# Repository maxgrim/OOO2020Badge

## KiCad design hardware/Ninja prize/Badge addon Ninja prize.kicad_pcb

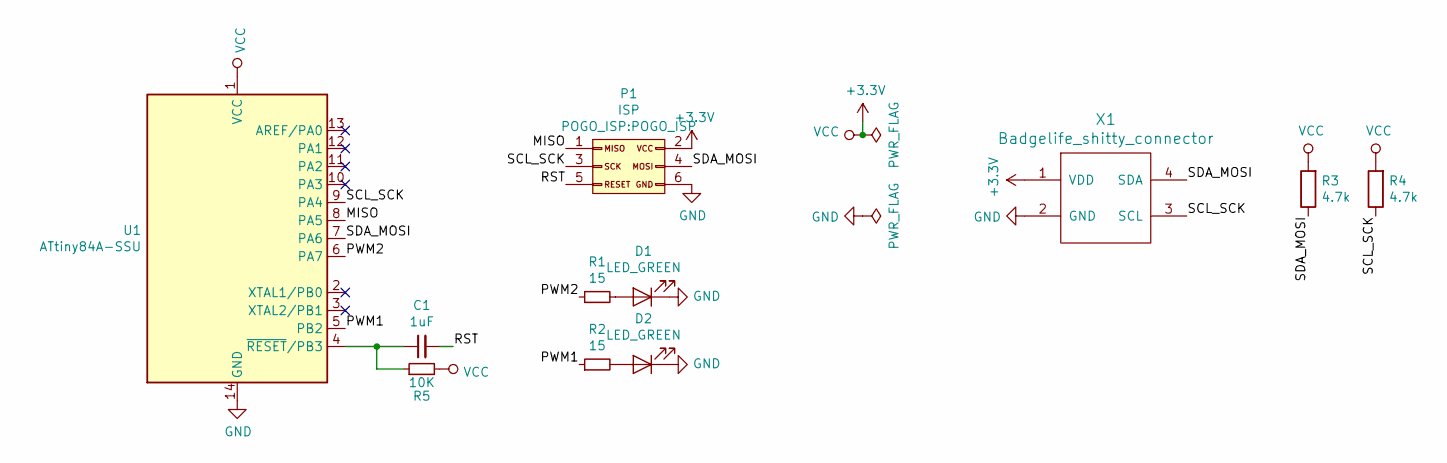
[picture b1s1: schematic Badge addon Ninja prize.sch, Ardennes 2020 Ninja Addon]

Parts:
C1: 1uF; C_0603_1608Metric; LCSC Part C15849
D1, D2: LED_GREEN; LED_1206_3216Metric_Castellated; LCSC Part C375461
P1: ISP; POGO_ISP; JLCPCB BOM 0
R1, R2: 15; R_0603_1608Metric; LCSC Part C23204
R3, R4: 4.7k; R_0603_1608Metric; LCSC Part C23162
R5: 10K; R_0603_1608Metric; LCSC Part C15401
U1: ATtiny84A-SSU; SOIC-14_3.9x8.7mm_P1.27mm; LCSC Part C144333
X1: Badgelife_shitty_connector; Badgelife-Shitty-2x2; JLCPCB BOM 0

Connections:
+3V3: P1.2, R3.2, R4.2, R5.2, U1.1 (VCC), X1.1 (VDD)
/MISO: P1.1, U1.8 (PA5)
/PWM1: R2.1, U1.5 (PB2)
/PWM2: R1.1, U1.6 (PA7)
/RST: C1.2, P1.5
/SCL_SCK: P1.3, R4.1, U1.9 (PA4), X1.3 (SCL)
/SDA_MOSI: P1.4, R3.1, U1.7 (PA6), X1.4 (SDA)
GND: D1.1 (K), D2.1 (K), P1.6, U1.14 (GND), X1.2 (GND)
unnamed: C1.1, R5.1, U1.4 (~RESET~/PB3)
unnamed: D1.2 (A), R1.2
unnamed: D2.2 (A), R2.2

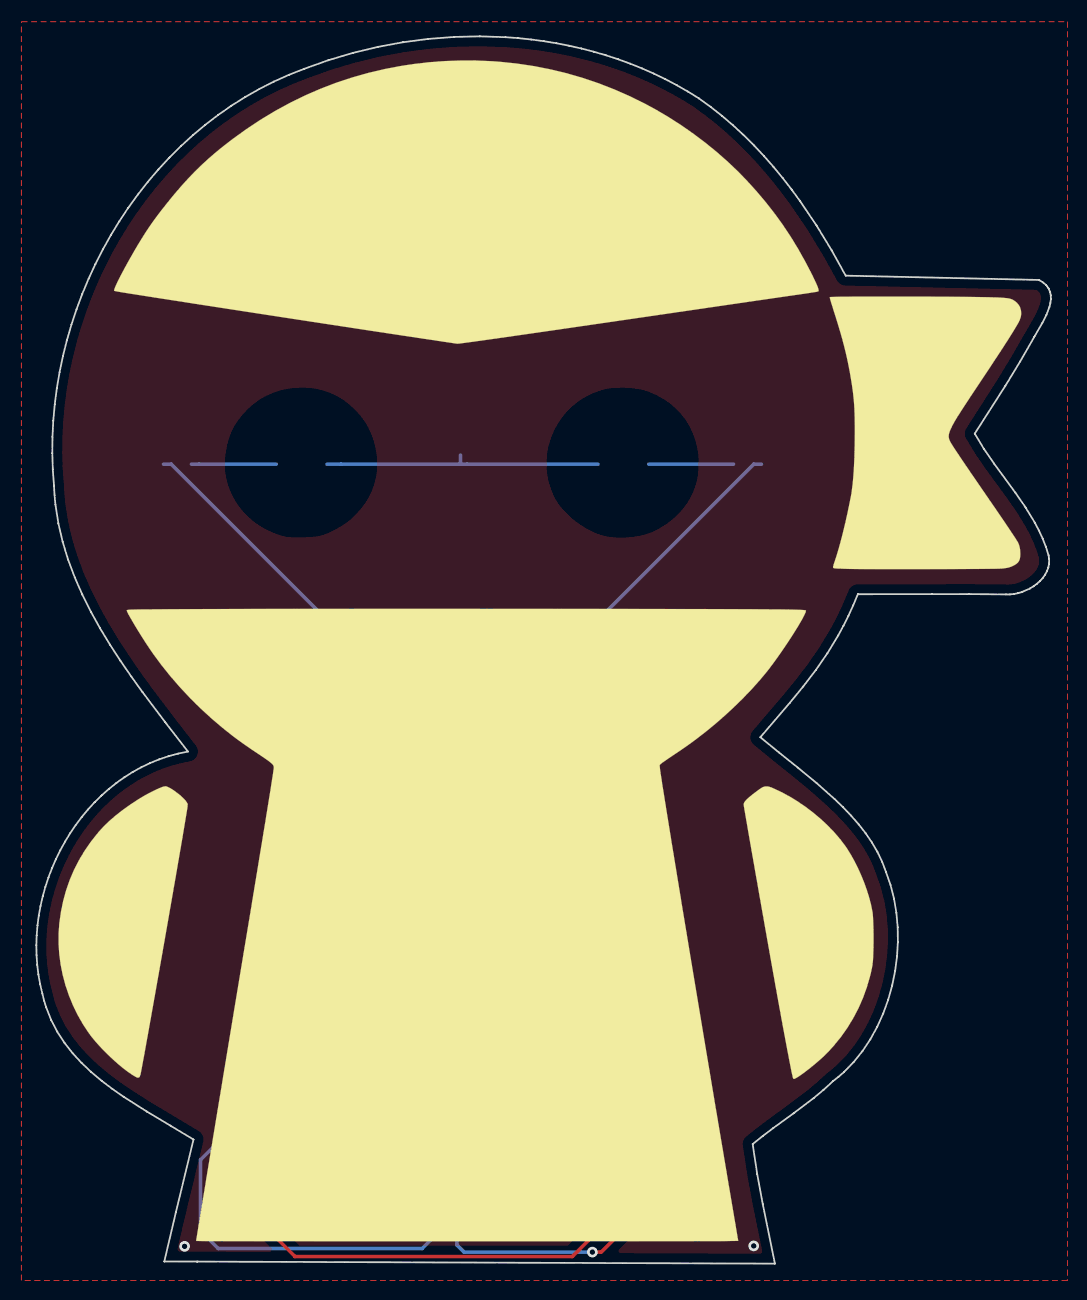
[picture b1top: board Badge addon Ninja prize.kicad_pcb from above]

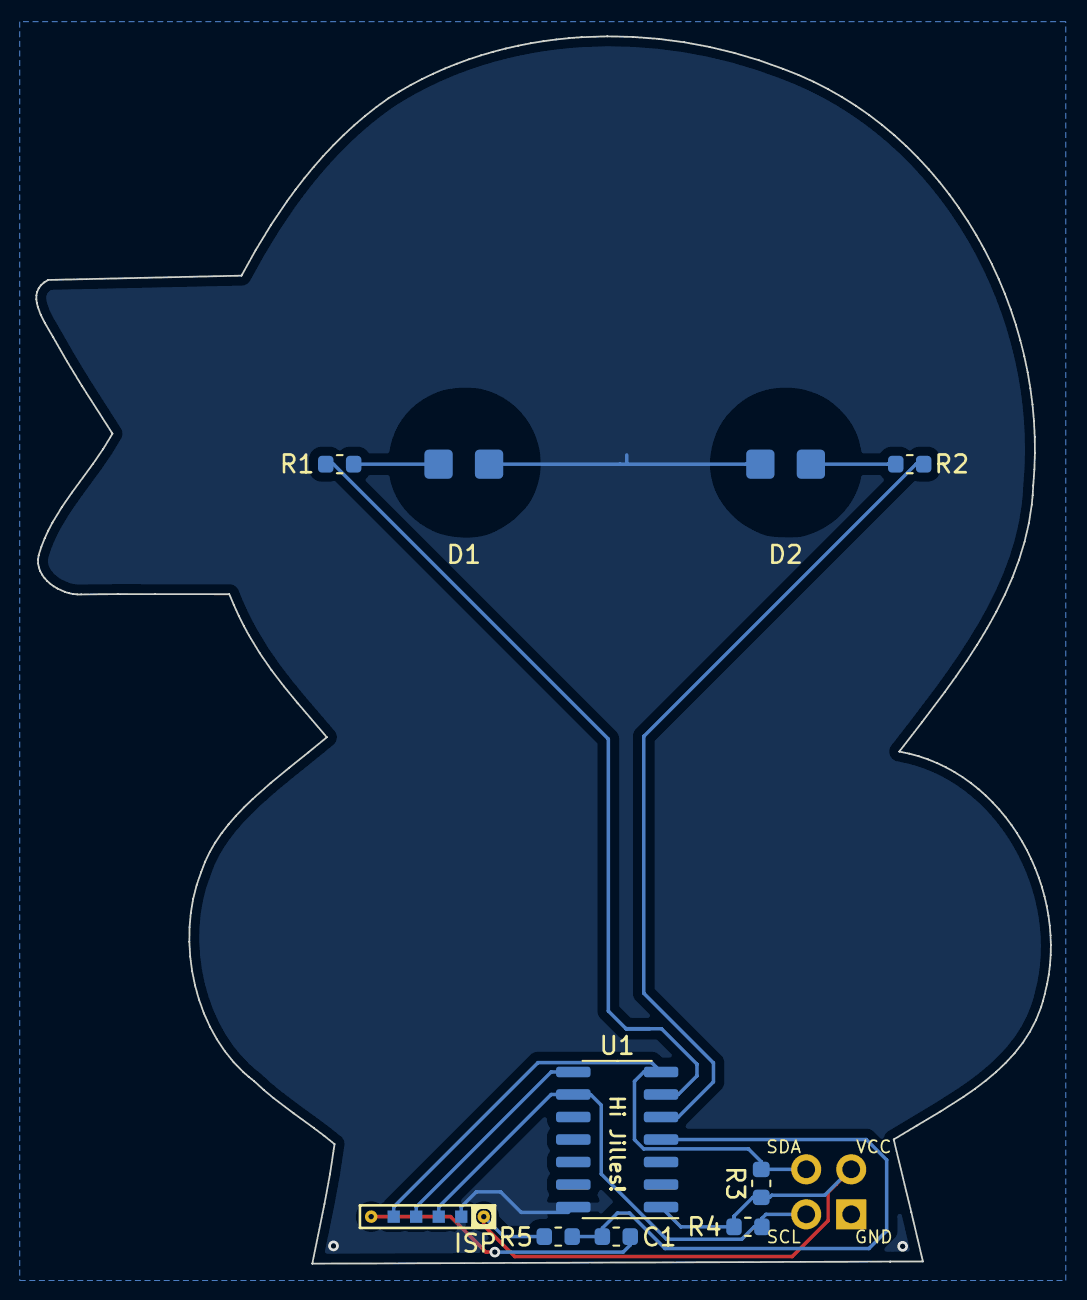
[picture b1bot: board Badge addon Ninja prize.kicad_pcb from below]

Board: 2 copper layers, 57.2 x 69.2 mm, 12 parts (10 on the bottom side), 11 nets.

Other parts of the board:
Ref**: Val**; ninja-art

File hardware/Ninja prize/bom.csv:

Comment,Designator,Footprint,LCSC Part #,Quantity
"1uF Unpolarized capacitor, small symbol",C1,C_0603_1608Metric,C15849,1
LED_GREEN Light emitting diode,"D1,D2",LED_1206_3216Metric_Castellated,C375461,2
"15 Resistor, small symbol","R1,R2",R_0603_1608Metric, C23204,2
4.7k Resistor,"R3,R4",R_0603_1608Metric,C23162,2
"10K Resistor, small symbol",R5,R_0603_1608Metric,C15401,1
"ATtiny84A-SSU 20MHz, 8kB Flash, 512B SRAM, 512B EEPROM, debugWIRE, SOIC-14",U1,SOIC-14_3.9x8.7mm_P1.27mm,C144333,1

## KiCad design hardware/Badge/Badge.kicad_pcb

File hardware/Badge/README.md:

import placement_helpers

# For LEDs
placement_helpers.place_circle(["D1", "D2", "D3", "D4", "D5", "D6", "D7", "D8", "D9", "D10", "D11", "D12"], 0, (250, 250), 1325)

# For capacitors
placement_helpers.place_circle(["C1", "C2", "C4", "C7", "C8", "C9", "C11", "C12", "C13", "C14", "C15", "C15"], 0, (250, 250), 1290)

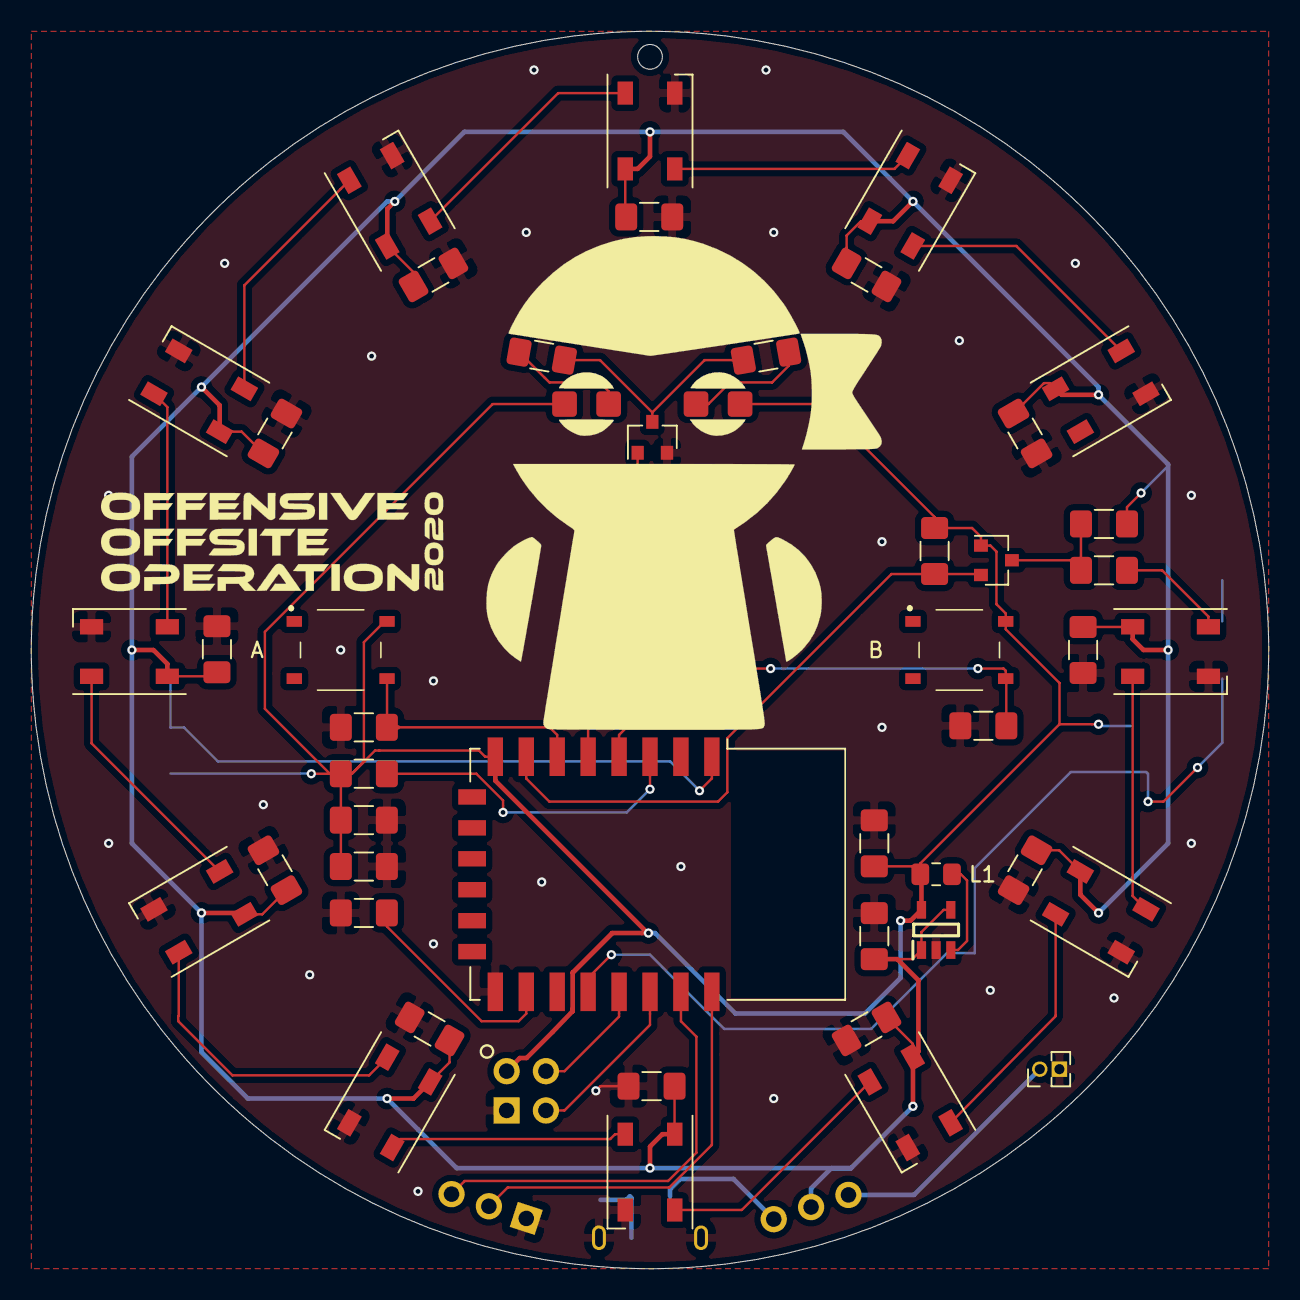
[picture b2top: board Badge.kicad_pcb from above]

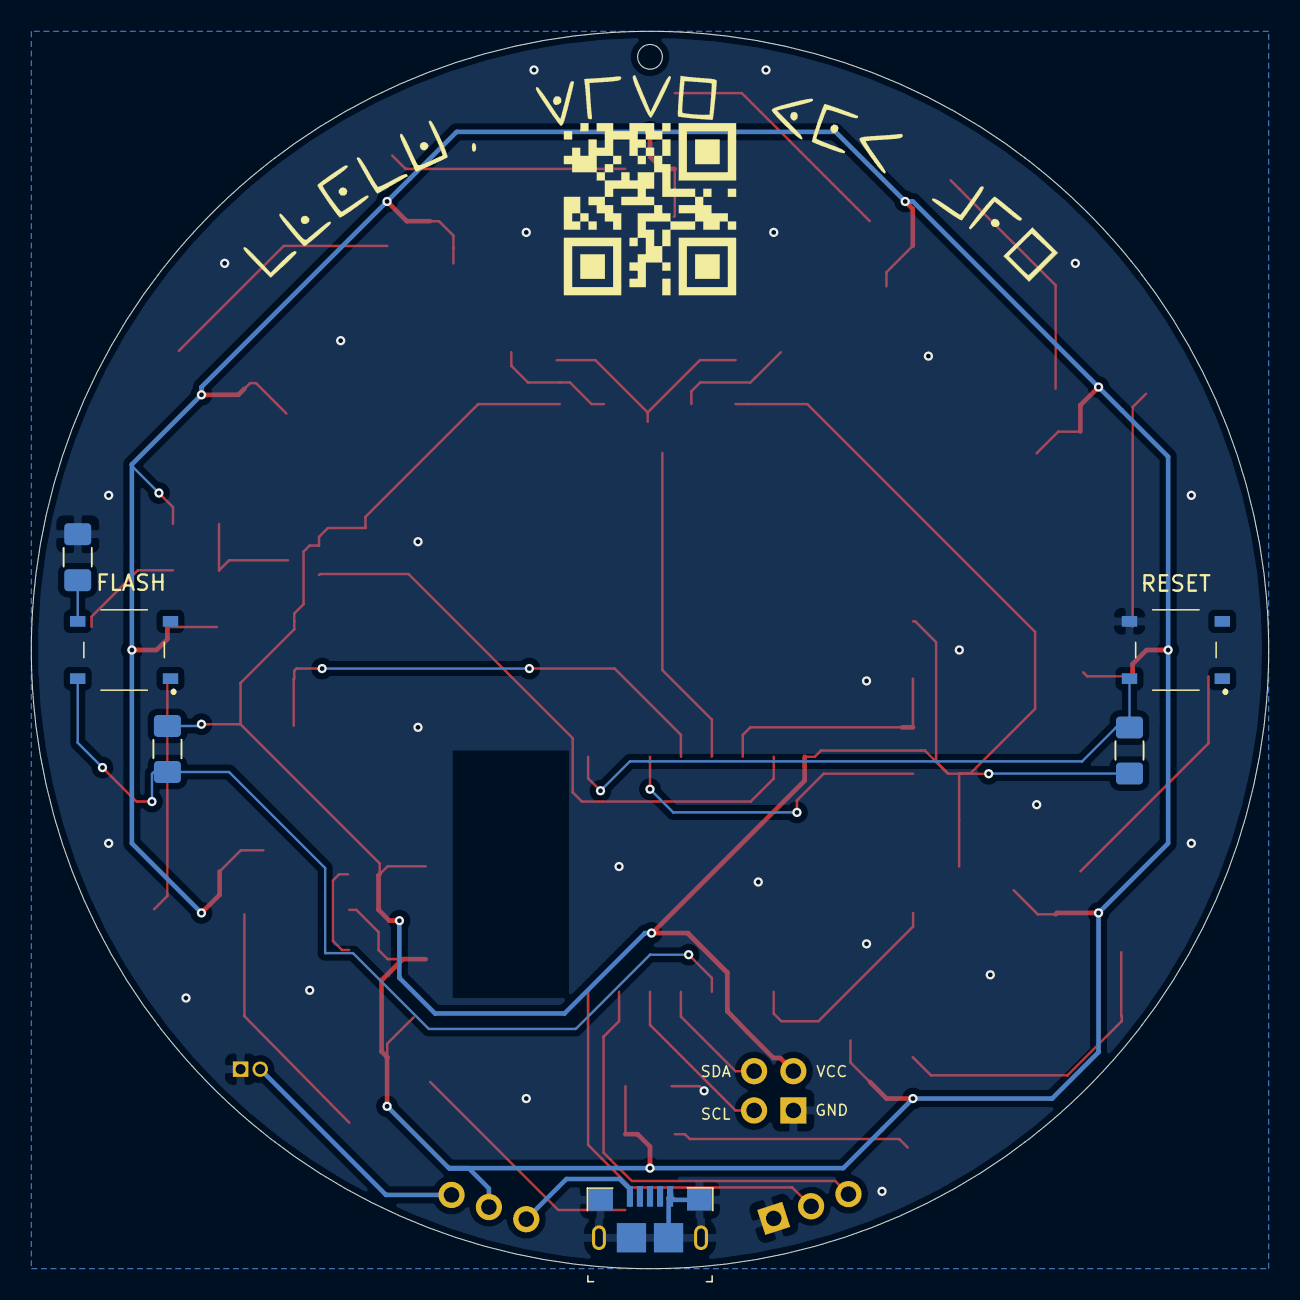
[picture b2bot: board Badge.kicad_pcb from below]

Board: 2 copper layers, 80.0 x 80.0 mm, 56 parts (6 on the bottom side), 35 nets.

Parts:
C1, C2, C4, C5, C7, C8, C9, C11, C12, C13, C14, C15, C16: 0.1uF; C_1206_3216Metric_Pad1.42x1.75mm_HandSolder
C3, C6, C10: 10uF; C_1206_3216Metric_Pad1.42x1.75mm_HandSolder
D1, D2, D3, D4, D5, D6, D7, D8, D9, D10, D11, D12: WS2812B; LED_WS2812B_PLCC4_5.0x5.0mm_P3.2mm
D13, D14: RED; LED_1206_3216Metric_Castellated
J1: FTDI; PinHeader_1x03_P2.54mm_Vertical
J2: PowerSelect; PinHeader_1x03_P2.54mm_Vertical
J3: 10118193-0001LF; USB_Micro_B_Female_10118193-0001LF
J4: Battery mount; PinHeader_1x02_P1.27mm_Vertical
L1: 4.7uH; L_0805_2012Metric_Pad1.15x1.40mm_HandSolder
PS1: PAM2301CAAB330; SOT95P280X110-5N
Q1, Q2: BSS138LT1G; SOT-23
R1, R9: 56; R_1206_3216Metric_Pad1.42x1.75mm_HandSolder
R1#2, R2, R3, R4, R6, R7, R12, R13: 10K; R_1206_3216Metric_Pad1.42x1.75mm_HandSolder
R8: 470; R_1206_3216Metric_Pad1.42x1.75mm_HandSolder
R11: 300; R_1206_3216Metric_Pad1.42x1.75mm_HandSolder
S1: RESET; PTS526SM15SMTR2LFS
S2: FLASH; PTS526SM15SMTR2LFS
S3: BUTTON_A; PTS526SM15SMTR2LFS
S4: BUTTON_B; PTS526SM15SMTR2LFS
U1: ESP-12E
X1: Badgelife_shitty_connector; Badgelife-Shitty-2x2

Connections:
+3V3: C3.1, C5.1, C10.1, D13.2, D14.2, L1.2, PS1.5, Q1.1, R1#2.1, R2.2, R6.1, R7.1, S3.2, S4.2, U1.8, X1.1
/BATT+: J2.3, J4.1
/DIN_HIGH: Q1.3, R3.2, R11.2
/DIN_LOW: Q1.2, R2.1, U1.7
/GPIO0: R7.2, S2.2, U1.18
/GPIO12: R12.1, S3.4, U1.6
/GPIO14: Q2.1, U1.5
/GPIO16: R13.1, S4.4, U1.4
/PWR_IN: C1.1, C2.1, C4.1, C6.1, C7.1, C8.1, C9.1, C11.1, C12.1, C13.1, C14.1, C15.1, C16.1, D1.1, D2.1, D3.1, D4.1, D5.1, D6.1, D7.1, D8.1, D9.1, D10.1, D11.1, D12.1, J2.2, PS1.1, PS1.4, R3.1
/RST: R6.2, S1.2, U1.1
/RX: J1.3, U1.21
/SCL: U1.20, X1.3
/SDA: U1.19, X1.4
/TX: J1.2, U1.22
/USB+: J2.1, J3.1
GND: C1.2, C2.2, C3.2, C4.2, C5.2, C6.2, C7.2, C8.2, C9.2, C10.2, C11.2, C12.2, C13.2, C14.2, C15.2, C16.2, D1.3, D2.3, D3.3, D4.3, D5.3, D6.3, D7.3, D8.3, D9.3, D10.3, D11.3, D12.3, J1.1, J3.5, J3.SH, J4.2, PS1.2, Q2.2, R4.2, R8.1, R12.2, R13.2, S1.4, U1.15, X1.2
unnamed: D1.2, D2.4
unnamed: D1.4, R11.1
unnamed: D2.2, D3.4
unnamed: D3.2, D4.4
unnamed: D4.2, D5.4
unnamed: D5.2, D6.4
unnamed: D6.2, D7.4
unnamed: D7.2, D8.4
unnamed: D8.2, D9.4
unnamed: D10.2, D11.4
unnamed: D9.2, D10.4
unnamed: D11.2, D12.4
unnamed: D13.1, R9.1
unnamed: D14.1, R1.1
unnamed: L1.1, PS1.3
unnamed: Q2.3, R1.2, R9.2
unnamed: R1#2.2, U1.3
unnamed: R4.1, U1.16
unnamed: R8.2, S2.4

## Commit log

2020-10-09 Added WLED submodule
2020-10-09 Added Badge library and PlatformIO override ini
2020-10-09 Added Adafruit's Neopixel library
2020-10-09 Added LEDCOUNT to platformio_override.ini
2020-10-09 Added TaskScheduler library
2020-10-29 Added PoC menu code
2020-10-29 Added WiFi initialization code
2020-10-29 Added Crypto module
2020-10-29 Added Debug and Definitions header files
2020-10-29 Added RGB module
2020-10-29 Added SerialPrompt module
2020-10-29 Added Settings module
2020-10-29 Added Morse module
2020-10-29 Removed failing dependency from SerialPrompt
2020-10-29 Updated Badge code
2020-10-29 Added empty CatchTheLed code
2020-10-29 Updated WLED submodule
2020-10-29 Updated platformio_override.ini
2020-10-29 Edit printlns modified: lib/Badge/src/Challenges/Morse.cpp modified: lib/Badge/src/SerialPrompt.cpp
2020-10-29 YAML file for hackazon new file: ooo_badge_hackazon.yaml
2020-10-29 Removed unused RGB loop
2020-10-29 Improved menu button handling
2020-10-29 Updated SerialPrompt
2020-10-29 Added SPIFFs flag
2020-10-29 Updated Morse
2020-10-29 Added base code for FastCalculation
2020-10-29 Updated CatchTheLed base code
2020-10-29 Added button handling for CombinationLock
2020-10-29 Added sample code
2020-10-29 Added cat flag.txt challenge to SerialPrompt
2020-10-29 Renamed Hackazon file to challenge.yaml
2020-10-29 Added Webserver basis code
2020-10-29 Moved rgbSetup function
2020-10-29 Moved ooo_badge_hackazon.yaml to challenge.yaml
2020-10-29 Added RasterDungeon setup code
2020-10-31 Bugfix in deactivateMenu
2020-10-31 Updated RGB methods
2020-10-31 Added RasterDungeon to menu
2020-10-31 Made detectButtonChange static
2020-10-31 Added eyes functionality
2020-10-31 Migrated badge init code to Eyes functionality
2020-10-31 Reformatting
2020-10-31 Bugfix in WLED check
2020-10-31 Added menu animation and updated RGB functionality
2020-10-31 Removed obsolete comments
2020-10-31 Modified LED conversion
2020-10-31 Updated CombinationLock setup code
2020-10-31 Updated Morse to reflect the updates
2020-10-31 Added RasterDungeon challenge
2020-10-31 By adding lib_deps we don't need the submodules anymore
2020-10-31 Updated WLED
2020-10-31 Menu will later activate webserver challenge
2020-10-31 Moved Crypto to FlagCrypto
2020-10-31 Added AES encrypted flag to RasterDungeon
2020-10-31 Only print dungeon layout in DEBUG mode
2020-10-31 Added serial output
2020-10-31 Remove unused handle
2020-11-01 Updated badge example code
2020-11-01 Added disable call to morse task
2020-11-01 Updated RasterDungeon
2020-11-01 Added code for requesting sole execution
2020-11-01 Updated AES crypto methods
2020-11-01 Improved SerialPrompt
2020-11-01 Made EEPROM boot modes more clear
2020-11-01 Added usermod for badge default settings
    This will make sure that WLED is configured with the christmas effect as default
2020-11-01 Moved WiFi setup in Badge setup code
2020-11-01 Updated WLED patch
2020-11-01 Replaced 0 with TASK_IMMEDIATE
2020-11-01 Added first code for webserver challenge
2020-11-01 Updated WLED effect settings
2020-11-09 Renamed RasterDungeon to SpaceMaze
2020-11-09 Renamed usermod for badge and added button support
2020-11-10 Removed submodules
2020-11-10 Updated WLED support and added final effects
2020-11-10 Removed submodules from .gitmodules
2020-11-10 Updated initial effects
2020-11-11 Added challenges to menu
2020-11-11 Added menu options
2020-11-11 Made blink menu confirmation faster
2020-11-11 Updated SpaceMaze
    Added grid image and removed unused variables
2020-11-11 Updated combination lock
2020-11-11 Added combination lock to prompt
2020-11-11 macOS .gitignore
2020-11-11 Renamed CombinationLock to LaserController
2020-11-11 Updated LaserController
2020-11-11 Limited menu options
2020-11-11 Updated SpaceMaze
2020-11-11 Updated webserver
2020-11-14 Added SpaceInvaders game
2020-11-14 Updated / renamed FastCalculation to WhizKid
2020-11-14 DoneCallback null check
2020-11-14 Added WhizKid to the menu
2020-11-14 Added Filesystem challenge
2020-11-14 Cleaned up FlagCrypto
2020-11-14 Added Nicki
2020-11-14 Updated CatchTheLed
2020-11-14 Added RGB_DEFAULT_BRIGHTNESS
2020-11-14 Added margin to game
2020-11-14 Added original source code for game
2020-11-14 Added animations to CatchTheLed
2020-11-14 Remove dual serialPromptActivate
2020-11-14 uint8_t to uint16_t
2020-11-14 Renamded printMaze to printDungeon
2020-11-14 Changed type of variable
2020-11-14 Actually print out the flag for CatchTheLed
2020-11-14 Added space to flag WhizKid print
2020-11-14 Clarified SerialPrompt command
2020-11-14 Compressed gratz.png
2020-11-14 Remove unused flag
2020-11-14 Added stego challenge source
2020-11-14 Added badge hardware
2020-11-14 Added OOObot
2020-11-14 Renamed challenges
2020-11-14 Updated RainMan
2020-11-14 Updated admin to captain
2020-11-14 Added new themed prompt
2020-11-14 Updated FS challenge
2020-11-14 Changed some commands
2020-11-14 Added Rick stego link
2020-11-14 Updated morse contents
2020-11-14 BugFix SpaceMaze
2020-11-14 To lowercase
2020-11-14 Add Python command
2020-11-14 Mistake
2020-11-15 Remove extra challenge
2020-11-15 Fix serial python command
2020-11-15 AP setup changed
2020-11-15 Fix argument handling in serial prompt
2020-11-15 Add win animation to SpaceXTerminator
2020-11-15 Blink less for SpaceMaze
2020-11-15 Only print RainMen answer in DEBUG
2020-11-15 Update RainMen
2020-11-17 Updated badge usermod
2020-11-17 Actually use eepromStartAddress in Settings
2020-11-17 Updated example code
2020-11-17 Reduce SRAM usage
2020-11-17 WLED: Revert "Patch: Set mDNS field empty by default"
2020-11-17 Added DNS server support to webserver
2020-11-17 Minified webserver HTML
2020-11-17 Cosmetic fix in serial print
2020-11-17 Updated vscode settings
2020-11-17 Added basic flashing script
2020-11-17 Added Hackazon flags + explanation
2020-11-17 Added PDF of schematics
2020-11-17 Updated flash.sh
2020-11-20 Updated hardware
2020-11-20 Updated flash script and (hopefully) uploaded final firmware
2020-11-22 Fixed crashes for displaying flags
2020-11-22 Reset timer on fail in SpaceXTerminator
2020-11-22 Made SpaceXTerminator a little harder
2020-11-22 Added PoC to solve SpaceXTerminator
2020-11-22 Added Ninja prize code
2020-11-22 Reset the flag after XOR operation
2020-11-22 Updated firmware_1.0.bin
2020-11-23 Modified starships game
2020-11-23 Changed remote filename
2020-11-23 Don't turn eyes off at start of SpaceXTerminator
2020-11-23 Removed double new-line
2020-11-23 Updated firmware_1.0.bin and spiffs_1.0.bin
2020-11-23 Remove base64 from aesDecrypt
2020-11-23 Decoded base64 for encrypted flags
2020-11-25 Increased flash speed for script
2020-11-26 Added logo
2020-11-26 Created Hackazon challenge files
2020-12-07 Moved resources around
